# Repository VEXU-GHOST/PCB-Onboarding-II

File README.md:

# PCB-Onboarding-II
Repo for the second part of PCB onboarding of the VEXU GHOST hardware team

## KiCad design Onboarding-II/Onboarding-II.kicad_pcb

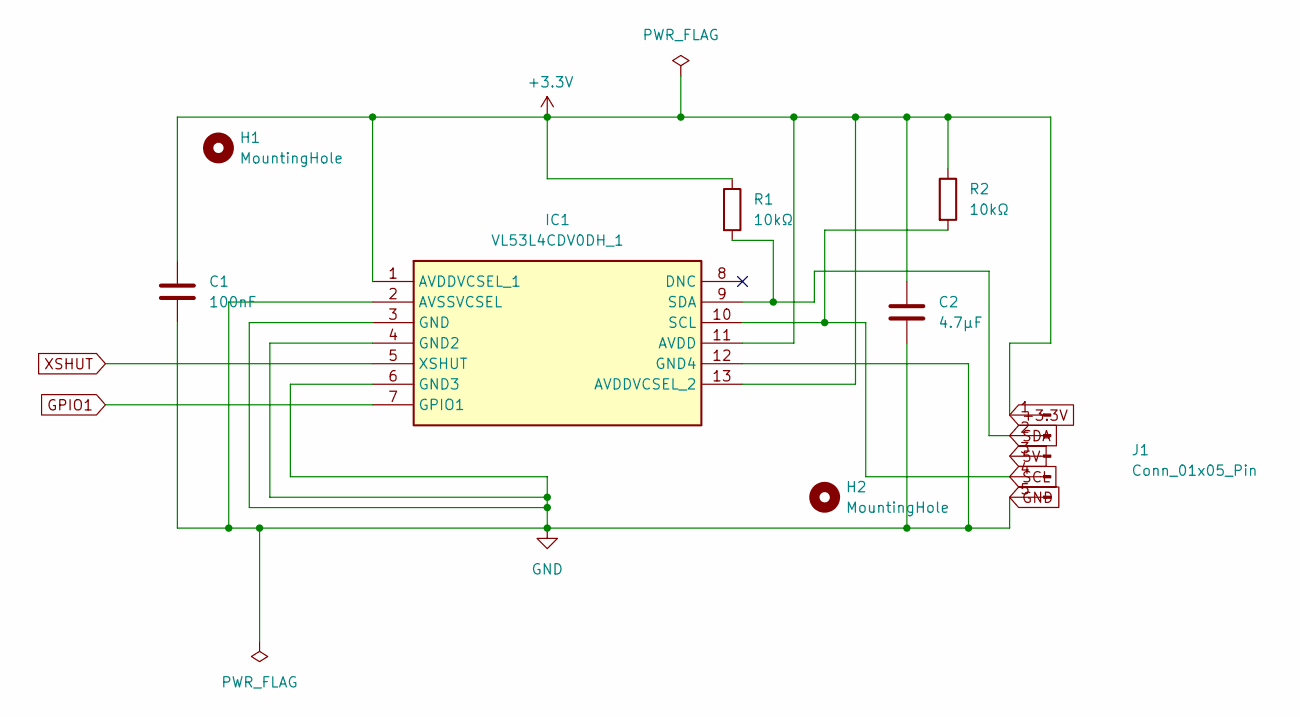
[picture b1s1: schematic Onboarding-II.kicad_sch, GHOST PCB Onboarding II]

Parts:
C1: 100nF; C_0805_2012Metric
C2: 4.7µF; C_0805_2012Metric
H1, H2: MountingHole; MountingHole_3.2mm_M3
IC1: VL53L4CDV0DH_1; VL53L4CDV0DH1; Manufacturer_Part_Number VL53L4CDV0DH/1; Mouser Part Number 511-VL53L4CDV0DH/1
J1: Conn_01x05_Pin; PinSocket_1x05_P2.54mm_Vertical
R1, R2: 10kΩ; R_0805_2012Metric

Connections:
5V: J1.3
+3.3V: C1.1, C2.1, IC1.1 (AVDDVCSEL_1), IC1.11 (AVDD), IC1.13 (AVDDVCSEL_2), J1.1, R1.1, R2.1
GND: C1.2, C2.2, IC1.2 (AVSSVCSEL), IC1.3 (GND), IC1.4 (GND2), IC1.6 (GND3), IC1.12 (GND4), J1.5
GPIO1: IC1.7 (GPIO1)
SCL: IC1.10 (SCL), J1.4, R2.2
SDA: IC1.9 (SDA), J1.2, R1.2
XSHUT: IC1.5 (XSHUT)

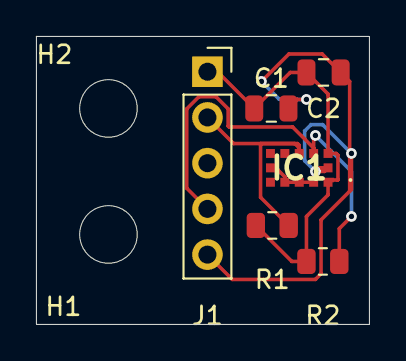
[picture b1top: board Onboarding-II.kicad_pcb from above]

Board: 2 copper layers, 18.5 x 16.0 mm, 8 parts (0 on the bottom side), 4 nets.

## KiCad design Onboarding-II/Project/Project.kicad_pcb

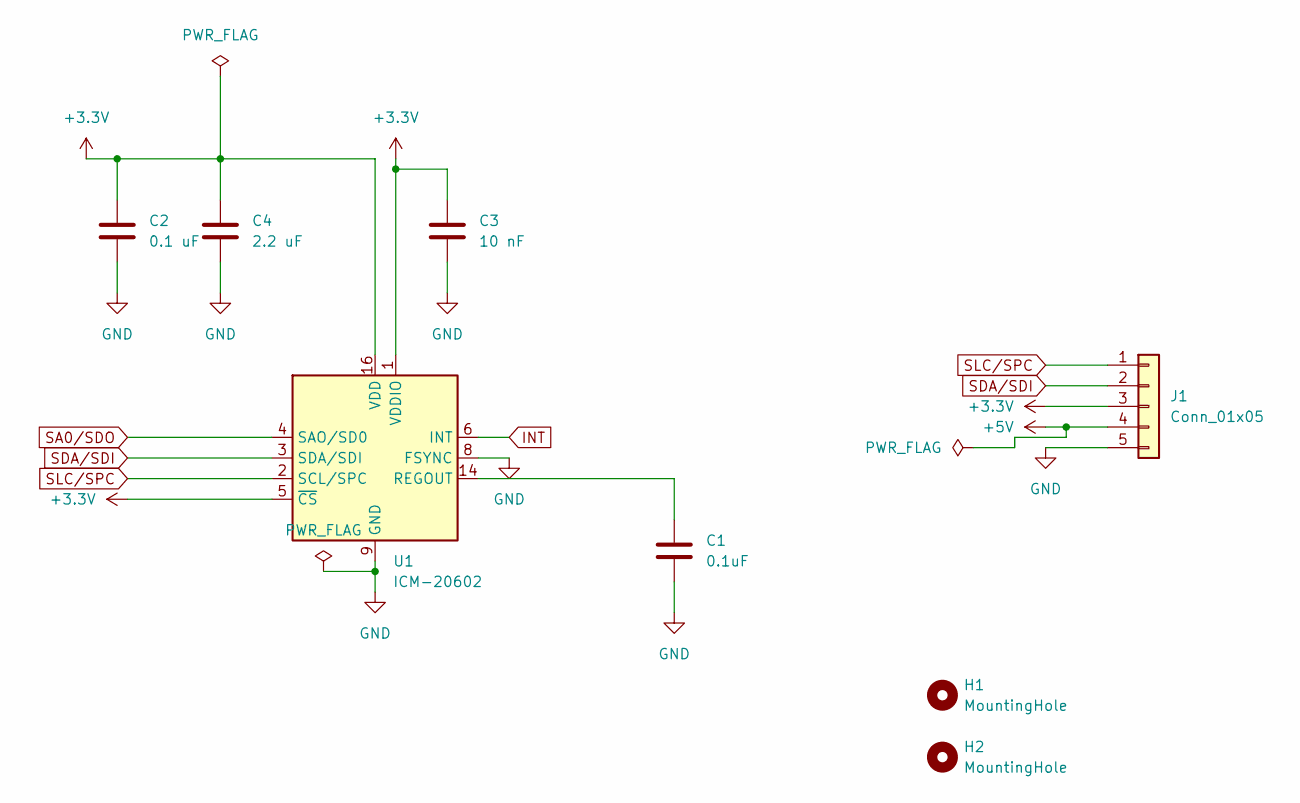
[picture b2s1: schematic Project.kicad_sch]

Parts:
C1: 0.1uF; C_0603_1608Metric
C2: 0.1 uF; C_0603_1608Metric
C3: 10 nF; C_0603_1608Metric
C4: 2.2 uF; C_0603_1608Metric
H1, H2: MountingHole; MountingHole_3.2mm_M3
J1: Conn_01x05; PinHeader_1x05_P2.54mm_Horizontal
U1: ICM-20602; LGA-16_3x3mm_P0.5mm_LayoutBorder3x5y

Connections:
+3.3V: C2.1, C3.1, C4.1, J1.3, U1.1 (VDDIO), U1.5 (~CS), U1.16 (VDD)
+5V: J1.4
GND: C1.2, C2.2, C3.2, C4.2, J1.5, U1.8 (FSYNC), U1.9 (GND), U1.10 (GND), U1.11 (GND), U1.12 (GND), U1.13 (GND), U1.15 (GND)
INT: U1.6 (INT)
unnamed: C1.1, U1.14 (REGOUT)
SA0/SDO: U1.4 (SAO/SD0)
SDA/SDI: J1.2, U1.3 (SDA/SDI)
SLC/SPC: J1.1, U1.2 (SCL/SPC)

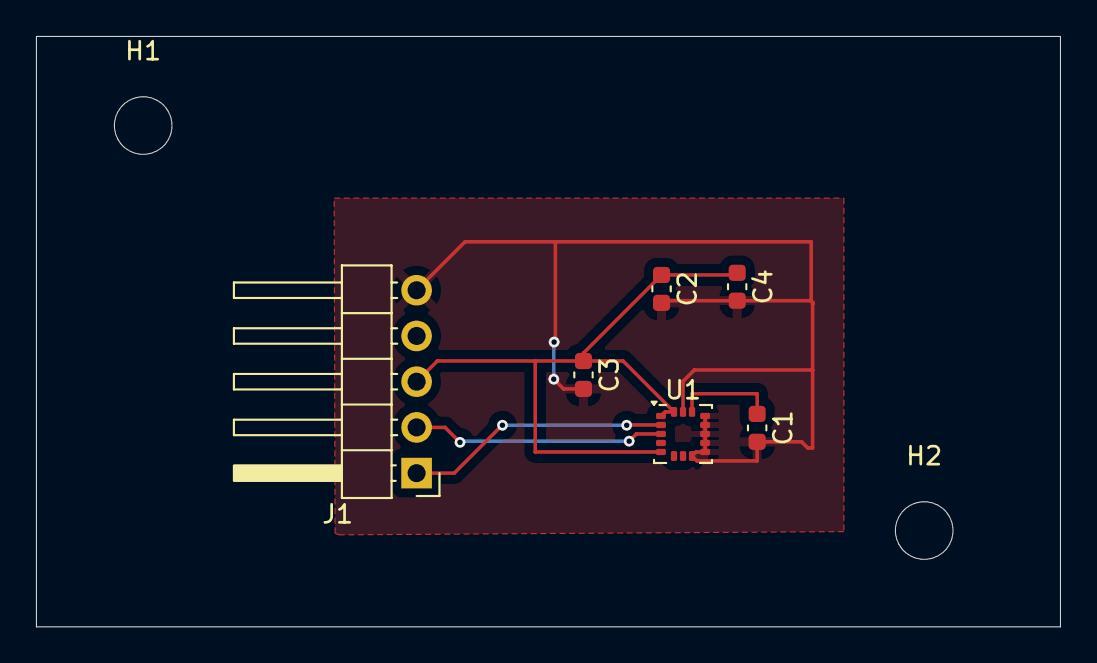
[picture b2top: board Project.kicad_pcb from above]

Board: 2 copper layers, 56.9 x 32.8 mm, 8 parts (0 on the bottom side), 5 nets.
